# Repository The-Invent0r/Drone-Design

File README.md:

# Custom Drone flight controller PCB and radio controller + all software.

## Overview
This is a custom flight controller I designed and built for a brushed DC motor drone, powered by an ATmega328p microcontroller, nRF24l01 radio, and MPU6050 IMU. I wanted a hands-on challenge to merge my skills in PCB design, microcontrollers, and motor control—after a year of troubleshooting, it flies stable and takes wireless commands.

## Features
- Real-time stabilization using MPU6050 gyro and accelerometer data.  
- Wireless control via nRF24l01 at 2.4GHz.  
- Drives four brushed DC motors with custom MOSFET-based drivers.  
- Lightweight 4-layer PCB with EMI shielding and efficient power distribution.

## Design & Build
- **Hardware**:  
  - *ATmega328p*: Familiar, handles PWM, I2C, and SPI for motors, IMU, and radio. Runs at 3.7V (LiPo)—tested stable at 16MHz, no boost converter needed.  
  - *MPU6050*: 3-axis gyro and accelerometer for flight dynamics.  
  - *nRF24l01*: 2.4GHz radio for ground station comms.  
  - *IRLML2502 MOSFETs*: Low Rds, fast-switching drivers for four motors, with Schottky flyback diodes.  
  - *1S 90C LiPo*: Powers it all; ditched regulators after testing.  
- **PCB**: Started with a 2-layer board, but motor EMI kept resetting the MCU. Switched to a 4-layer design—motor drivers on bottom, sensitive components on top, ground/power planes in between for shielding, I also tried a 6-layer board which worked just as well as the 4-layer board.
- **Tools**: KiCAD for schematics and PCB layout, soldering iron and heat gun for assembly, Multiwii open-source software for fast firmware.  
- **Challenges**:  
  - EMI from motors crashed the MCU. Tried a 5V boost converter—didn’t help. Went 3.7V direct from LiPo, still issues.  
  - 4-layer and 6-layer PCB rethink separated high-current and signal paths—killed the resets.

## Results
Breadboard tests nailed stable motor control; bench sims proved IMU-driven stabilization. It’s rough but works—tweaking PWM is next for smoother flight.

## Media
4-layer board

6-layer board

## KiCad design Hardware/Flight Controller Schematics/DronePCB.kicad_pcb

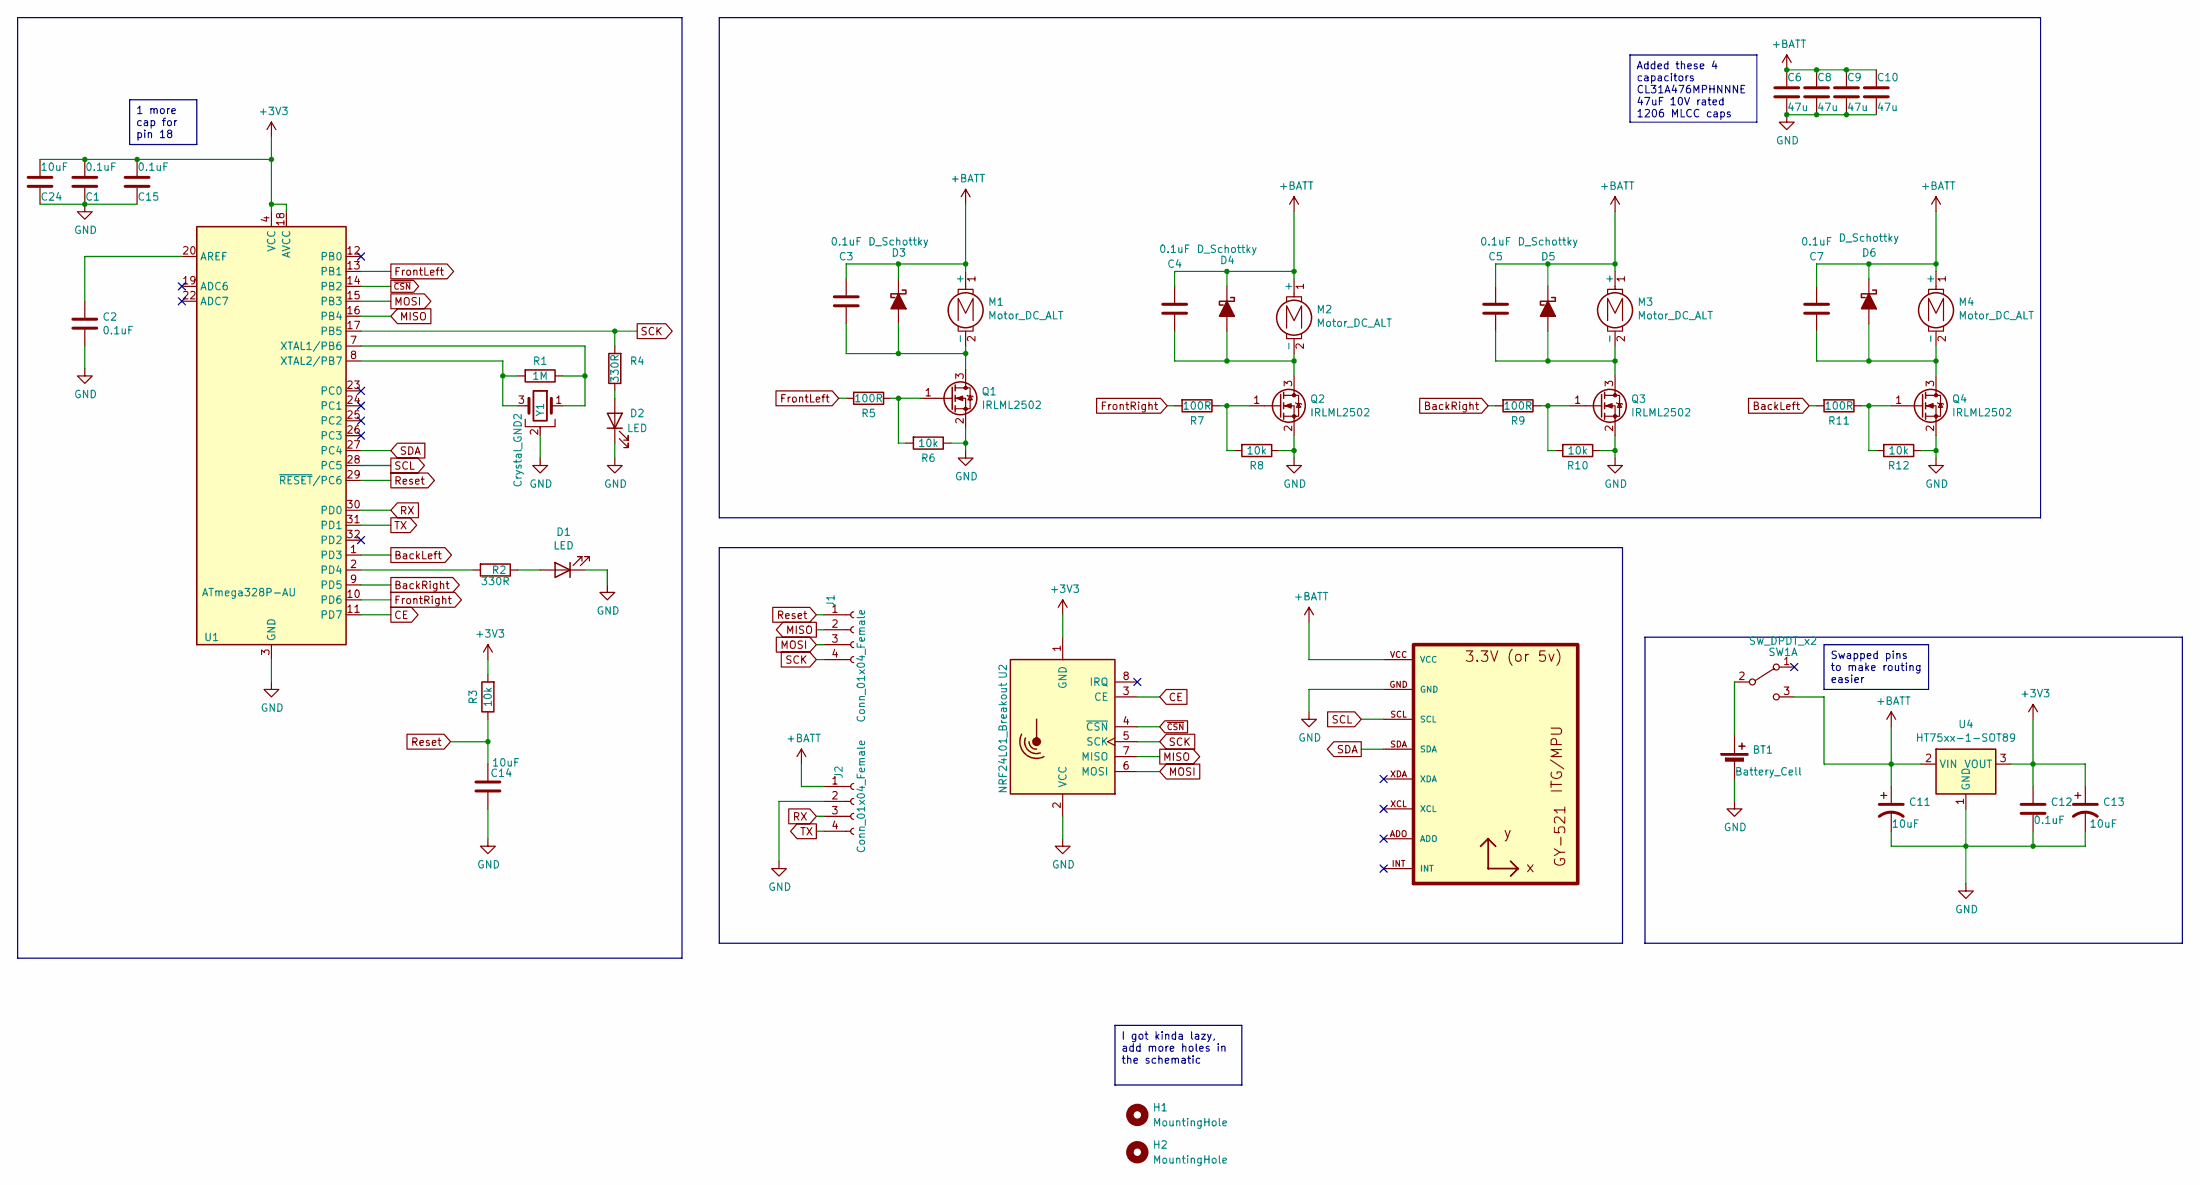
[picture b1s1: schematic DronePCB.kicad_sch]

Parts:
BT1: Battery_Cell; PinHeader_1x02_P2.54mm_Vertical
C1, C2, C3, C4, C5, C7, C12, C15: 0.1uF; C_0805_2012Metric_Pad1.18x1.45mm_HandSolder
C6, C8, C9, C10: 47u; C_1206_3216Metric_Pad1.33x1.80mm_HandSolder
C11, C13: 10uF; CP_EIA-3216-10_Kemet-I
C14, C24: 10uF; C_0805_2012Metric_Pad1.18x1.45mm_HandSolder
D1, D2: LED; LED_0805_2012Metric_Pad1.15x1.40mm_HandSolder
D3, D4, D5, D6: D_Schottky; D_1206_3216Metric_Pad1.42x1.75mm_HandSolder
H1, H2: MountingHole; MountingHole_2.2mm_M2
J1, J2: Conn_01x04_Female; PinHeader_1x04_P2.54mm_Vertical
M1, M2, M3, M4: Motor_DC_ALT; PinHeader_1x02_P2.54mm_Vertical
Q1, Q2, Q3, Q4: IRLML2502; SOT-23
R1: 1M; R_0805_2012Metric_Pad1.20x1.40mm_HandSolder
R2, R4: 330R; R_0805_2012Metric_Pad1.20x1.40mm_HandSolder
R3, R6, R8, R10, R12: 10k; R_0805_2012Metric_Pad1.20x1.40mm_HandSolder
R5, R7, R9, R11: 100R; R_0805_2012Metric_Pad1.20x1.40mm_HandSolder
SW1: SW_DPDT_x2; SW_SPDT_PCM12
U1: ATmega328P-AU; TQFP-32_7x7mm_P0.8mm
U2: NRF24L01_Breakout; NRF24L01-Module-SMD
U3: GY-521
U4: HT75xx-1-SOT89; SOT-89-3
Y1: Crystal_GND2; Resonator_SMD_muRata_CSTxExxV-3Pin_3.0x1.1mm

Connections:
+3V3: C1.2, C12.1, C13.1, C15.2, C24.2, R3.2, U1.4 (VCC), U1.6 (VCC), U1.18 (AVCC), U2.1 (GND), U4.3 (VOUT)
+BATT: C3.1, C4.1, C5.1, C6.1, C7.1, C8.1, C9.1, C10.1, C11.1, D3.1 (K), D4.1 (K), D5.1 (K), D6.1 (K), J2.1, M1.1 (+), M2.1 (+), M3.1 (+), M4.1 (+), SW1.3 (C), U3.VCC, U4.2 (VIN)
BackLeft: R11.2, U1.1 (PD3)
BackRight: R9.2, U1.9 (PD5)
CE: U1.11 (PD7), U2.3 (CE)
FrontLeft: R5.2, U1.13 (PB1)
FrontRight: R7.2, U1.10 (PD6)
GND: BT1.2 (-), C1.1, C2.2, C6.2, C8.2, C9.2, C10.2, C11.2, C12.2, C13.2, C14.2, C15.1, C24.1, D1.1 (K), D2.1 (K), J2.2, Q1.2 (S), Q2.2 (S), Q3.2 (S), Q4.2 (S), R6.1, R8.1, R10.1, R12.1, U1.3 (GND), U1.5 (GND), U1.21 (GND), U2.2 (VCC), U3.GND, U4.1 (GND), Y1.2
MISO: J1.2, U1.16 (PB4), U2.7 (MISO)
MOSI: J1.3, U1.15 (PB3), U2.6 (MOSI)
unnamed: BT1.1 (+), SW1.2 (B)
unnamed: D1.2 (A), R2.1
unnamed: D2.2 (A), R4.1
unnamed: C3.2, D3.2 (A), M1.2 (-), Q1.3 (D)
unnamed: C4.2, D4.2 (A), M2.2 (-), Q2.3 (D)
unnamed: C5.2, D5.2 (A), M3.2 (-), Q3.3 (D)
unnamed: C7.2, D6.2 (A), M4.2 (-), Q4.3 (D)
unnamed: Q1.1 (G), R5.1, R6.2
unnamed: Q2.1 (G), R7.1, R8.2
unnamed: Q3.1 (G), R9.1, R10.2
unnamed: Q4.1 (G), R11.1, R12.2
unnamed: C2.1, U1.20 (AREF)
unnamed: R2.2, U1.2 (PD4)
unnamed: R1.1, U1.7 (XTAL1/PB6), Y1.1
unnamed: R1.2, U1.8 (XTAL2/PB7), Y1.3
RX: J2.3, U1.30 (PD0)
Reset: C14.1, J1.1, R3.1, U1.29 (~RESET/PC6)
SCK: J1.4, R4.2, U1.17 (PB5), U2.5 (SCK)
SCL: U1.28 (PC5), U3.SCL
SDA: U1.27 (PC4), U3.SDA
TX: J2.4, U1.31 (PD1)
~CSN: U1.14 (PB2), U2.4 (~CSN)

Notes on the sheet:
1 more cap for pin 18
Added these 4 capacitors CL31A476MPHNNNE 47uF 10V rated 1206 MLCC caps
Swapped pins to make routing easier
I got kinda lazy, add more holes in the schematic

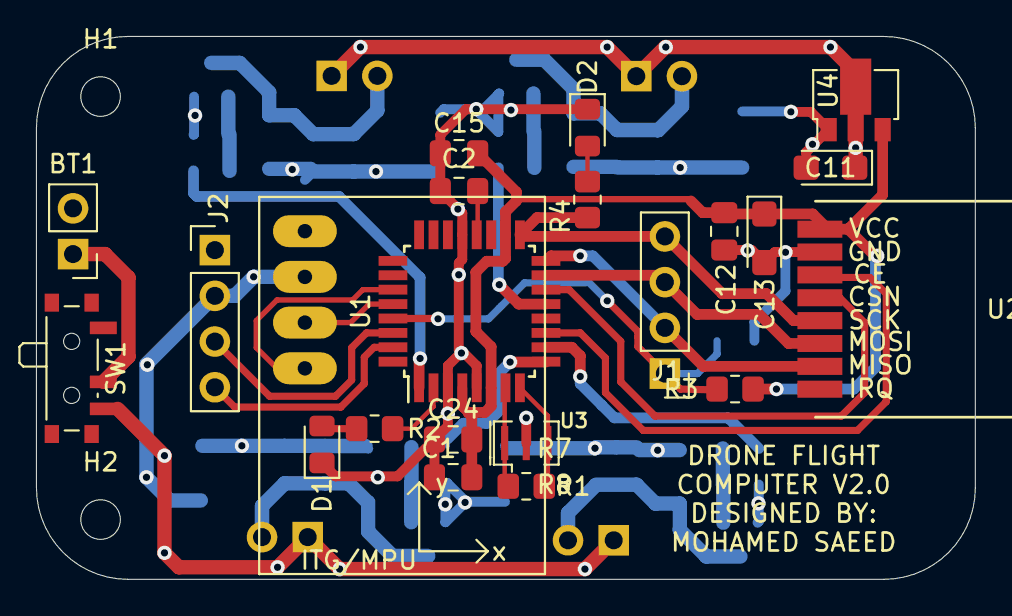
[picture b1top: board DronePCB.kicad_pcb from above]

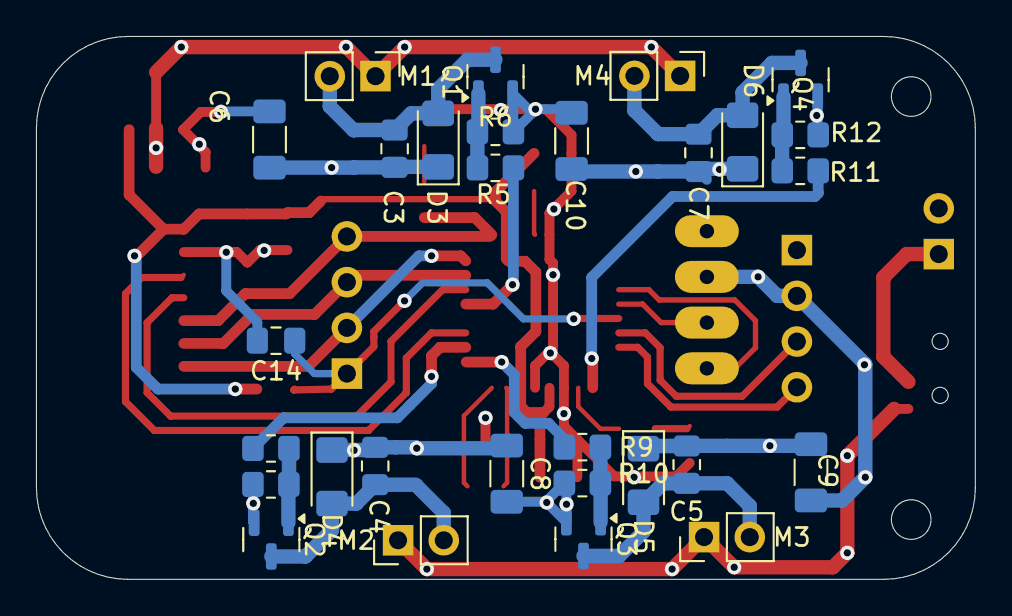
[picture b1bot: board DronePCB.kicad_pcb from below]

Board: 4 copper layers, 52.2 x 30.2 mm, 53 parts (29 on the bottom side), 32 nets.

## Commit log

2025-03-04 Update README.md
    writeup on drone project
2025-03-04 Create Readme
    flight controller schematics and files
2025-03-04 Create Remote Control
    remote control files
2025-03-04 Create Readme
    remote control schematic and files
2025-03-04 Create Readme
    flight controller software
2025-03-04 Create Readme
    remote control software
2025-03-06 Create Flight Controller Schematics
    flight controller hardware schematics
2025-03-06 Create Readme
    flight controller schematics
2025-03-06 Create Readme
    remote controller schematics
